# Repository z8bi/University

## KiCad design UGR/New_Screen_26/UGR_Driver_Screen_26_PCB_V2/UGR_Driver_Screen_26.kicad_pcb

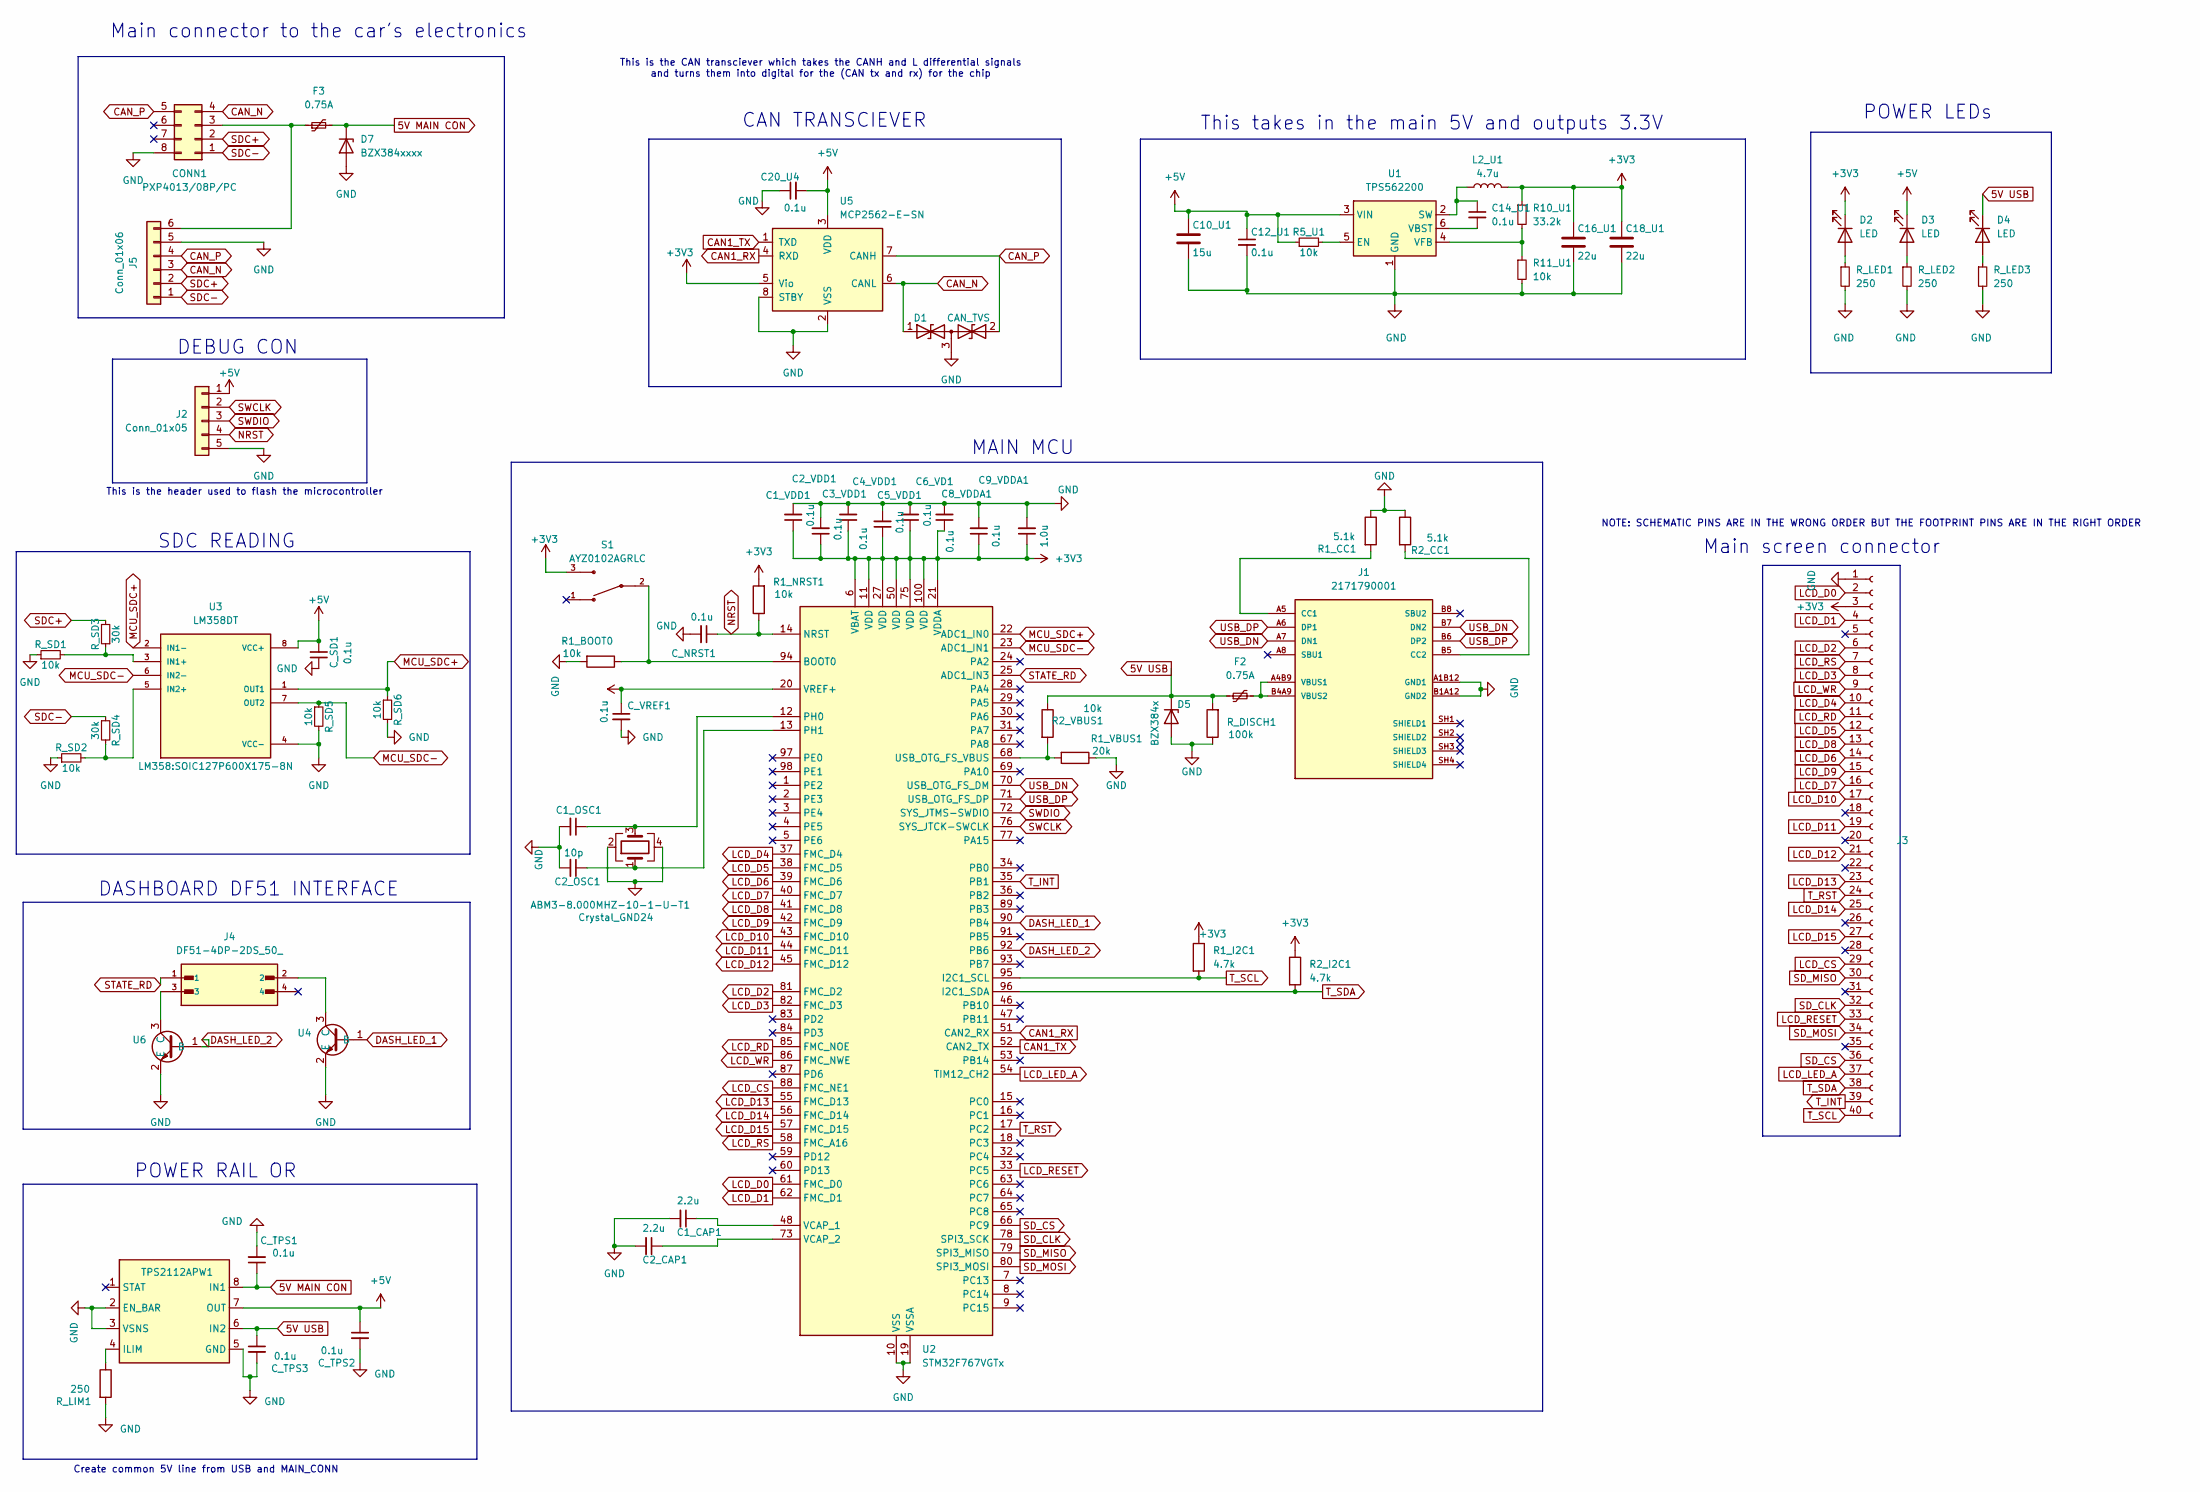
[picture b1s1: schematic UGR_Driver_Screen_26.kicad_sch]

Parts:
ABM3-8.000MHZ-10-1-U-T1: Crystal_GND24; Crystal_SMD_Abracon_ABM3B-4Pin_5.0x3.2mm
C1_CAP1, C2_CAP1: 2.2u; C_0603_1608Metric_Pad1.08x0.95mm_HandSolder
C1_OSC1, C2_OSC1: 10p; C_0603_1608Metric_Pad1.08x0.95mm_HandSolder
C1_VDD1, C2_VDD1, C3_VDD1, C4_VDD1, C5_VDD1, C6_VD1, C8_VDDA1, C12_U1, C14_U1, C20_U4: 0.1u; C_0603_1608Metric_Pad1.08x0.95mm_HandSolder
C9_VDDA1: 1.0u; C_0603_1608Metric_Pad1.08x0.95mm_HandSolder
C10_U1: 15u; C_1210_3225Metric_Pad1.33x2.70mm_HandSolder
C16_U1, C18_U1: 22u; C_1210_3225Metric_Pad1.33x2.70mm_HandSolder
CONN1: PXP4013/08P/PC; Bulgin_4000_PXP4013-08S-PC
C_NRST1: 0.1u; C_0603_1608Metric_Pad1.08x0.95mm_HandSolder
C_SD1: 0.1u; C_0603_1608Metric_Pad1.08x0.95mm_HandSolder
C_TPS1, C_TPS2, C_TPS3: 0.1u; C_0603_1608Metric_Pad1.08x0.95mm_HandSolder
C_VREF1: 0.1u; C_0603_1608Metric_Pad1.08x0.95mm_HandSolder
D1: CAN_TVS; SOT-23; Manufacturer Part No. SZNUP2105L
D2, D3, D4: LED; PinHeader_1x02_P2.54mm_Vertical
D5: BZX384x; D_SOD-323
D7: BZX384xxxx; D_SOD-323
F2, F3: 0.75A; Fuse_1812_4532Metric_Pad1.30x3.40mm_HandSolder; Manufacturer Part No. 1206L075/16WR
J1: 2171790001; MOLEX_2171790001; PARTREV A1
J2: Conn_01x05; PinHeader_1x05_P2.54mm_Vertical
J3: Conn_02x20_Socket; PinSocket_2x20_P2.54mm_Vertical
J4: DF51-4DP-2DS_50_; HIROSE_DF51-4DP-2DS_50_; PARTREV 1
J5: Conn_01x06; PinHeader_1x06_P2.54mm_Vertical
L2_U1: 4.7u; L_1206_3216Metric_Pad1.42x1.75mm_HandSolder
R1_BOOT0, R1_NRST1, R2_VBUS1, R5_U1, R11_U1: 10k; R_0603_1608Metric_Pad0.98x0.95mm_HandSolder
R1_CC1, R2_CC1: 5.1k; R_0603_1608Metric_Pad0.98x0.95mm_HandSolder
R1_I2C1, R2_I2C1: 4.7k; R_0603_1608Metric_Pad0.98x0.95mm_HandSolder
R1_VBUS1: 20k; R_0603_1608Metric_Pad0.98x0.95mm_HandSolder
R10_U1: 33.2k; R_0603_1608Metric_Pad0.98x0.95mm_HandSolder
R_DISCH1: 100k; R_0603_1608Metric_Pad0.98x0.95mm_HandSolder
R_LED1, R_LED2, R_LED3: 250; R_0603_1608Metric_Pad0.98x0.95mm_HandSolder
R_LIM1: 250; R_0603_1608Metric_Pad0.98x0.95mm_HandSolder
R_SD1, R_SD2, R_SD5, R_SD6: 10k; R_0603_1608Metric_Pad0.98x0.95mm_HandSolder
R_SD3, R_SD4: 30k; R_0603_1608Metric_Pad0.98x0.95mm_HandSolder
S1: AYZ0102AGRLC; SW_AYZ0102AGRLC
TPS2112APW1: SOP65P640X120-8N
U1: TPS562200; SOT-23-6
U2: STM32F767VGTx; LQFP-100_14x14mm_P0.5mm
U3: LM358DT; SOIC127P600X175-8N
U4, U6: SOT95P237X111-3N
U5: MCP2562-E-SN; SOIC-8_3.9x4.9mm_P1.27mm

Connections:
5V MAIN CON: C_TPS1.1, D7.1 (K), F3.2, TPS2112APW1.8 (IN1)
5V USB: C_TPS3.1, D4.1 (K), D5.1 (K), F2.1, R2_VBUS1.1, R_DISCH1.2, TPS2112APW1.6 (IN2)
+3V3: C1_VDD1.1, C2_VDD1.1, C3_VDD1.1, C4_VDD1.1, C5_VDD1.1, C6_VD1.1, C8_VDDA1.1, C9_VDDA1.1, C16_U1.1, C18_U1.1, C_VREF1.1, D2.1 (K), J3.3, L2_U1.2, R1_I2C1.1, R1_NRST1.2, R2_I2C1.1, R10_U1.1, S1.3, U2.6 (VBAT), U2.11 (VDD), U2.20 (VREF+), U2.21 (VDDA), U2.27 (VDD), U2.50 (VDD), U2.75 (VDD), U2.100 (VDD), U5.5 (Vio)
+5V: C10_U1.1, C12_U1.1, C20_U4.2, C_SD1.2, C_TPS2.1, D3.1 (K), J2.1, R5_U1.1, TPS2112APW1.7 (OUT), U1.3 (VIN), U3.8 (VCC+), U5.3 (VDD)
CAN1_RX: U2.51 (CAN2_RX), U5.4 (RXD)
CAN1_TX: U2.52 (CAN2_TX), U5.1 (TXD)
CAN_N: CONN1.4, D1.1 (A1), J5.3, U5.6 (CANL)
CAN_P: CONN1.5, D1.2 (A2), J5.4, U5.7 (CANH)
DASH_LED_1: U2.90 (PB4), U4.1 (B)
DASH_LED_2: U2.92 (PB6), U6.1 (B)
GND: ABM3-8.000MHZ-10-1-U-T1.2, ABM3-8.000MHZ-10-1-U-T1.4, C1_CAP1.2, C1_OSC1.2, C1_VDD1.2, C2_CAP1.2, C2_OSC1.2, C2_VDD1.2, C3_VDD1.2, C4_VDD1.2, C5_VDD1.2, C6_VD1.2, C8_VDDA1.2, C9_VDDA1.2, C10_U1.2, C12_U1.2, C16_U1.2, C18_U1.2, C20_U4.1, CONN1.8, C_NRST1.2, C_SD1.1, C_TPS1.2, C_TPS2.2, C_TPS3.2, C_VREF1.2, D1.3 (common), D5.2 (A), D7.2 (A), J1.A1B12 (GND1), J1.B1A12 (GND2), J2.5, J3.1, J5.5, R1_BOOT0.2, R1_CC1.1, R1_VBUS1.1, R2_CC1.1, R11_U1.2, R_DISCH1.1, R_LED1.2, R_LED2.2, R_LED3.2, R_LIM1.2, R_SD1.1, R_SD2.1, R_SD5.2, R_SD6.2, TPS2112APW1.2 (EN_BAR), TPS2112APW1.3 (VSNS), TPS2112APW1.5 (GND), U1.1 (GND), U2.10 (VSS), U2.19 (VSSA), U2.26 (VSS), U2.49 (VSS), U2.74 (VSS), U2.99 (VSS), U3.4 (VCC-), U4.2 (E), U5.2 (VSS), U5.8 (STBY), U6.2 (E); also elsewhere on the board
LCD_CS: J3.29, U2.88 (FMC_NE1)
LCD_D0: J3.2, U2.61 (FMC_D0)
LCD_D1: J3.4, U2.62 (FMC_D1)
LCD_D2: J3.6, U2.81 (FMC_D2)
LCD_D3: J3.8, U2.82 (FMC_D3)
LCD_D4: J3.10, U2.37 (FMC_D4)
LCD_D5: J3.12, U2.38 (FMC_D5)
LCD_D6: J3.14, U2.39 (FMC_D6)
LCD_D7: J3.16, U2.40 (FMC_D7)
LCD_D8: J3.13, U2.41 (FMC_D8)
LCD_D9: J3.15, U2.42 (FMC_D9)
LCD_D10: J3.17, U2.43 (FMC_D10)
LCD_D11: J3.19, U2.44 (FMC_D11)
LCD_D12: J3.21, U2.45 (FMC_D12)
LCD_D13: J3.23, U2.55 (FMC_D13)
LCD_D14: J3.25, U2.56 (FMC_D14)
LCD_D15: J3.27, U2.57 (FMC_D15)
LCD_LED_A: J3.37, U2.54 (TIM12_CH2)
LCD_RD: J3.11, U2.85 (FMC_NOE)
LCD_RESET: J3.33, U2.33 (PC5)
LCD_RS: J3.7, U2.58 (FMC_A16)
LCD_WR: J3.9, U2.86 (FMC_NWE)
MCU_SDC+: R_SD6.1, U2.22 (ADC1_IN0), U3.1 (OUT1), U3.2 (IN1-)
MCU_SDC-: R_SD5.1, U2.23 (ADC1_IN1), U3.6 (IN2-), U3.7 (OUT2)
NRST: C_NRST1.1, J2.4, R1_NRST1.1, U2.14 (NRST)
unnamed: CONN1.3, F3.1, J5.6
unnamed: D2.2 (A), R_LED1.1
unnamed: D3.2 (A), R_LED2.1
unnamed: D4.2 (A), R_LED3.1
unnamed 40: J1.A5 (CC1), R1_CC1.2; also elsewhere on the board
unnamed 41: J1.B5 (CC2), R2_CC1.2; also elsewhere on the board
unnamed 42: F2.2, J1.A4B9 (VBUS1), J1.B4A9 (VBUS2); also elsewhere on the board
unnamed: R_LIM1.1, TPS2112APW1.4 (ILIM)
unnamed: R5_U1.2, U1.5 (EN)
unnamed: C14_U1.1, L2_U1.1, U1.2 (SW)
unnamed: C14_U1.2, U1.6 (VBST)
unnamed: R10_U1.2, R11_U1.1, U1.4 (VFB)
unnamed: R1_BOOT0.1, S1.2, U2.94 (BOOT0)
unnamed: R1_VBUS1.2, R2_VBUS1.2, U2.68 (USB_OTG_FS_VBUS)
unnamed: ABM3-8.000MHZ-10-1-U-T1.3, C1_OSC1.1, U2.12 (PH0)
unnamed: ABM3-8.000MHZ-10-1-U-T1.1, C2_OSC1.1, U2.13 (PH1)
unnamed: C1_CAP1.1, U2.48 (VCAP_1)
unnamed: C2_CAP1.1, U2.73 (VCAP_2)
unnamed: R_SD1.2, R_SD3.1, U3.3 (IN1+)
unnamed: R_SD2.2, R_SD4.2, U3.5 (IN2+)
unnamed: J4.2, U4.3 (C)
unnamed: J4.3, U6.3 (C)
SDC+: CONN1.2, J5.2, R_SD3.2
SDC-: CONN1.1, J5.1, R_SD4.1
SD_CLK: J3.32, U2.78 (SPI3_SCK)
SD_CS: J3.36, U2.66 (PC9)
SD_MISO: J3.30, U2.79 (SPI3_MISO)
SD_MOSI: J3.34, U2.80 (SPI3_MOSI)
STATE_RD: J4.1, U2.25 (ADC1_IN3)
SWCLK: J2.2, U2.76 (SYS_JTCK-SWCLK)
SWDIO: J2.3, U2.72 (SYS_JTMS-SWDIO)
T_INT: J3.39, U2.35 (PB1)
T_RST: J3.24, U2.17 (PC2)
T_SCL: J3.40, R1_I2C1.2, U2.95 (I2C1_SCL)
T_SDA: J3.38, R2_I2C1.2, U2.96 (I2C1_SDA)
USB_DN: J1.A7 (DN1), J1.B7 (DN2), U2.70 (USB_OTG_FS_DM); also elsewhere on the board
USB_DP: J1.A6 (DP1), J1.B6 (DP2), U2.71 (USB_OTG_FS_DP); also elsewhere on the board

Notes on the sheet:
POWER RAIL OR
Create common 5V line from USB and MAIN_CONN
Main screen connector
POWER LEDs
MAIN MCU
This takes in the main 5V and outputs 3.3V
Main connector to the car's electronics
DASHBOARD DF51 INTERFACE
SDC READING
CAN TRANSCIEVER
This is the CAN transciever which takes the CANH and L differential signals and turns them into digital for the (CAN tx and rx) for the chip
This is the header used to flash the microcontroller
NOTE: SCHEMATIC PINS ARE IN THE WRONG ORDER BUT THE FOOTPRINT PINS ARE IN THE RIGHT ORDER
DEBUG CON

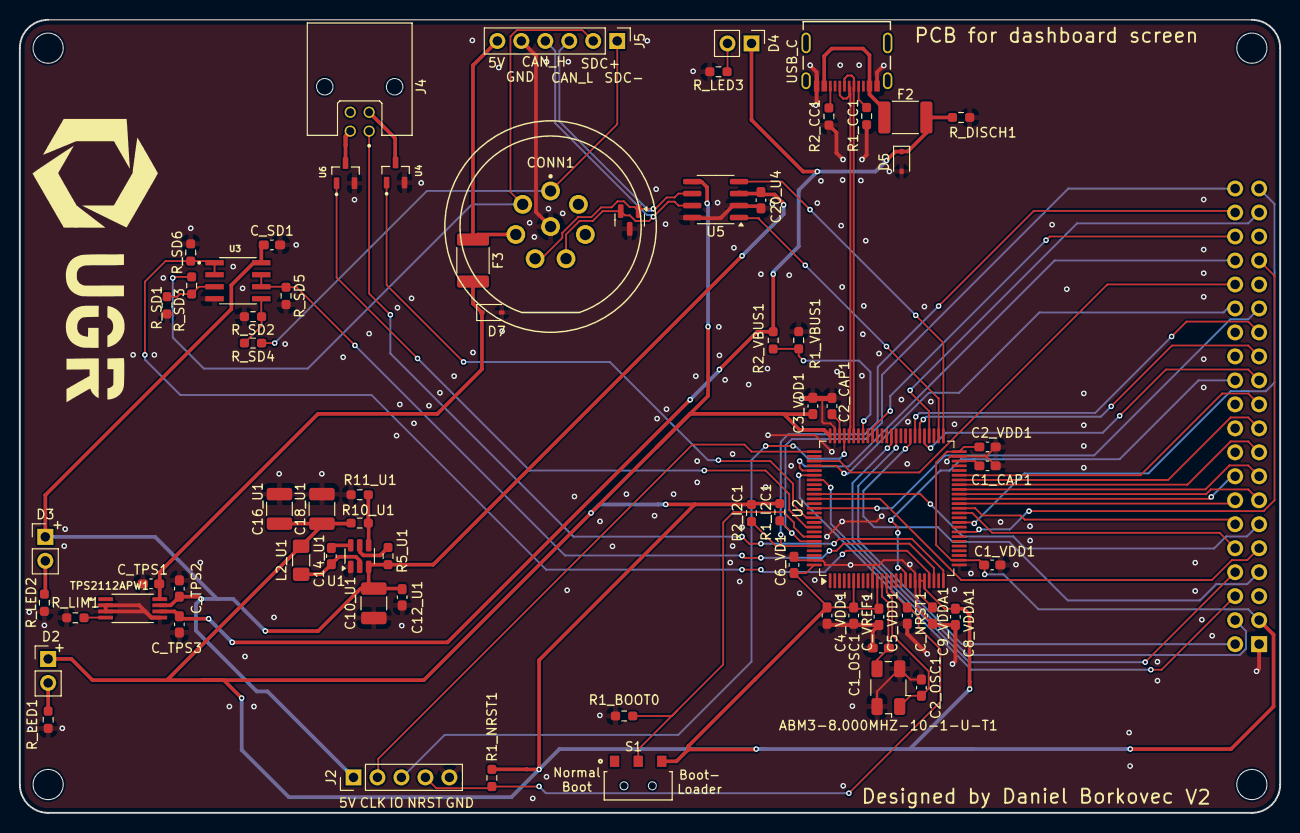
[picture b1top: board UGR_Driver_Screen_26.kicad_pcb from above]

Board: 2 copper layers, 133.5 x 84.0 mm, 74 parts (1 on the bottom side), 73 nets.

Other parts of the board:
MH_3.2mm, MH_3.2mm#2, MH_3.2mm#3, MH_3.2mm#4: MountingHole_3.2mm_M3
USB_C: 2171790001; MOLEX_2171790001

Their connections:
GND: USB_C.A1B12 (GND1), USB_C.B1A12 (GND2); also elsewhere on the board
unnamed 40: USB_C.A5 (CC1); also elsewhere on the board
unnamed 41: USB_C.B5 (CC2); also elsewhere on the board
unnamed 42: USB_C.A4B9 (VBUS1), USB_C.B4A9 (VBUS2); also elsewhere on the board
USB_DN: USB_C.A7 (DN1), USB_C.B7 (DN2); also elsewhere on the board
USB_DP: USB_C.A6 (DP1), USB_C.B6 (DP2); also elsewhere on the board

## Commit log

2026-02-09 Line Following V2
2026-02-09 Line Following V3
2026-02-11 Line Following V4
2026-02-16 Line Following V5 (color + Bluetooth)
2026-02-17 Line Following V4 FIX
2026-02-18 Line Following V5 - Bluetooth debug + Manual control
2026-02-19 Line Following V5 (Nicer code + all_pins.txt)
2026-02-19 edit
2026-02-19 Screen 26 code V2
2026-02-20 Rover V6 (parameter adjustment) + UGR Scenn 26 V2
2026-02-21 Slight updates to all
2026-02-21 Programming Stuff
2026-02-21 C:\Users\m4z3o\Desktop\University\Uni_Courses
2026-02-21 Programming Task 2 V1
2026-02-22 test
2026-02-22 Restructure
2026-02-27 Programming + Rover
2026-02-28 Ultrasonic Updates
2026-03-02 Rover Code Regactor
2026-03-02 refactor
2026-03-03 Refactor V2
2026-03-04 Ultrasonic working + Bluetooth
2026-03-04 Dualsense File Added
2026-03-05 Bluetooth Controller Fully Working
2026-03-09 New Blutooth + A.P. course stuff
2026-03-10 Advanced Programming Formative
2026-03-13 Full UGR Screen 26 Code + Rover
2026-03-13 Complete merge + Config changes
2026-03-15 Power Electronics + UGR Screen
2026-03-15 UGR Touch Screen Working
2026-03-15 New UGR Project Setup
2026-03-15 Remove tracked build artifacts
2026-03-15 Newest Gitignore
2026-03-15 New CMAKE
2026-03-16 new stuff
2026-03-16 FINALLY GOT FONTS WORKING ON UGR SCREEN
2026-03-18 Rover + Screen upgrades
2026-03-20 Automated Git Pull + Rover Start Switch
2026-03-20 UGR Logo work
2026-03-21 Decent UGR Screen Updates
2026-03-21 Prepped Screen for USB
2026-03-22 Additional USB features
2026-03-23 Rover Changes
2026-03-25 Final Rover Updates
2026-03-28 Rover + UGR Screen PCB
2026-03-28 Custom Libraries
2026-03-28 Screen V2
2026-03-28 Library Update
2026-03-28 Screen V2 Rev2
2026-03-28 Screen V2 Rev2_again
2026-03-28 KiCad Library Overhaul
2026-03-30 Better USB functionality as per V2 board
2026-03-30 Screen V2 updates
2026-03-30 Edit 2
2026-03-30 Better comments
2026-03-30 tic tac toe fix
2026-03-30 Final Changes
2026-03-30 Adv Prog Assignment 1 final changes
2026-04-05 Screen V2 REV2 changes
2026-04-07 Added Rover Board Files
2026-04-15 Power Updates
2026-04-15 All Power Labs Doc
2026-04-15 New Power Stuff
2026-04-15 Final Power PDF
2026-04-19 Programming Assignment 2 Begin
2026-04-19 Advanced Programming V1
2026-04-19 Latest Programming
2026-04-19 Linear Regression Done
2026-04-20 Logistic Regression Binary Start
2026-04-20 Binary Logistic Regression Done
2026-04-20 Documentation
2026-04-20 Documentation V2
2026-04-20 Linear Regression Polished
2026-04-20 Logistic Regression Futureproofing
2026-04-21 Programming Lectures
2026-04-21 Added time tracking to test.cpp
2026-04-21 Desktop Merge
2026-04-21 Resolve test.cpp conflict and keep logistic regression changes
